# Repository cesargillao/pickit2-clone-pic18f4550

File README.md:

# Clon del Programador de PIC PicKit 2 con PIC18F4550

## Se proporciona:
* Diagrama esquemático para emular el funcionamiento (Proteus)
* Diagrama esquemático y PCB (CadSoft Eagle)
* Software en C y ASM con su respectivo HEX (CCS Compiler)

### Si te gusta el proyecto, recomiendo dejar una estrella en el mismo o en mi perfil.
### Eso me inspira a seguir colaborando a la comunidad ❤.

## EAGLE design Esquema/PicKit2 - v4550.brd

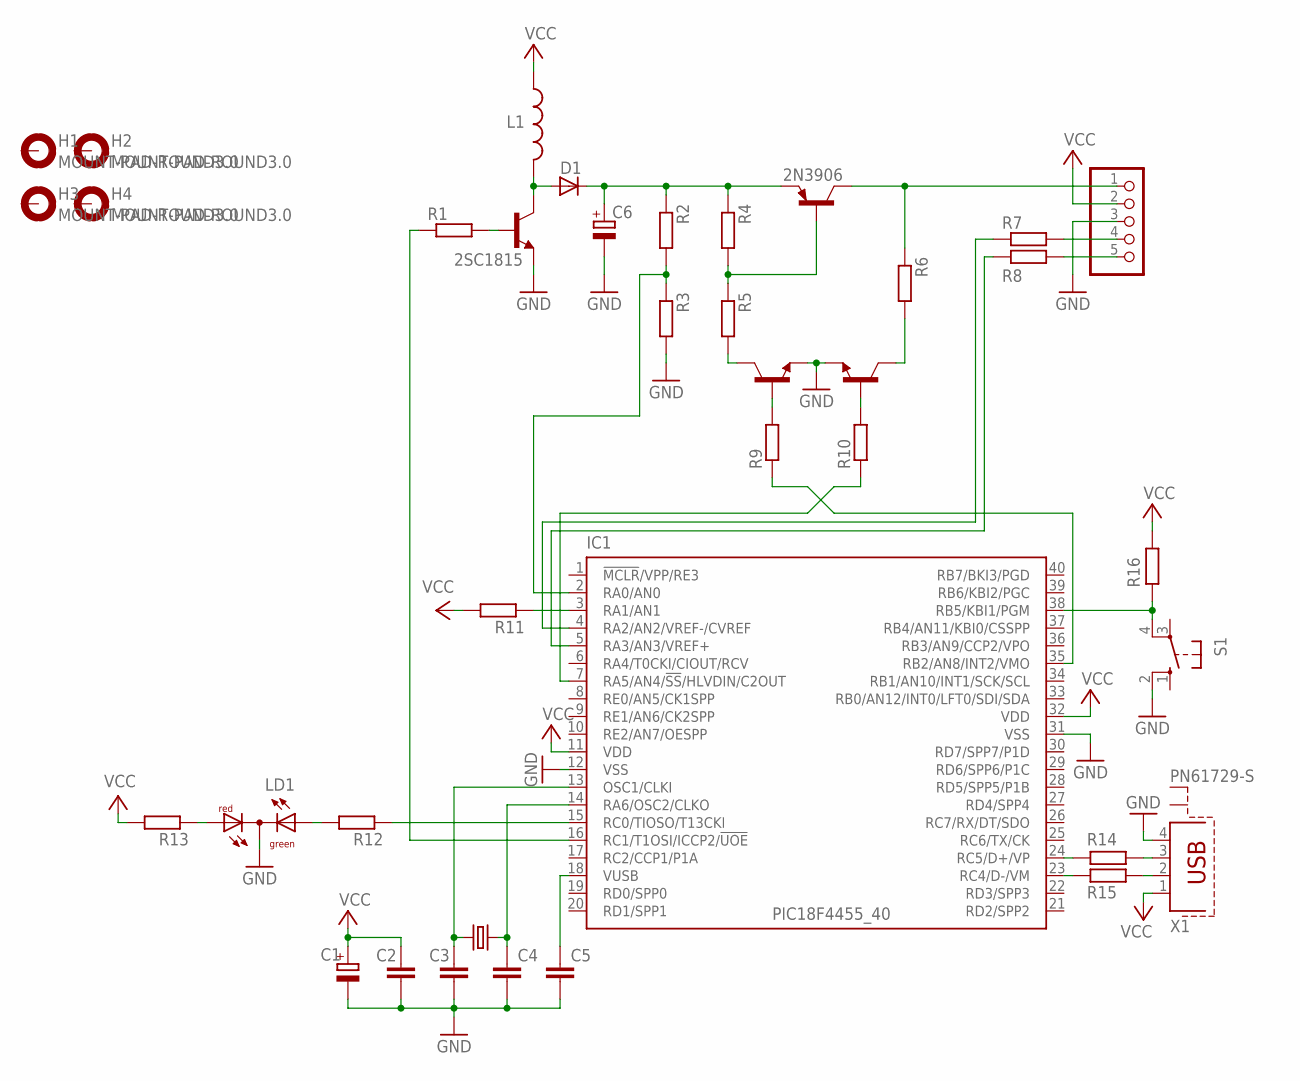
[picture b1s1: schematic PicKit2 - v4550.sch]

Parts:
C1, C6: CPOL-EUE2,5-6E; E2,5-6E
C2, C3, C4, C5: C-EU050-025X075; C050-025X075
D1: 1N4148DO35-10; DO35-10
H1, H2, H3, H4: MOUNT-PAD-ROUND3.0; 3,0-PAD
IC1: PIC18F4455_40; DIL40
JP1: PINHD-1X5/90; 1X05/90
L1: L-USIR-2; IR-2
LD1: DUOLED-RG-C; DUOLED-C-5MM
Q1: 2N3906; TO92
R1, R2, R3, R4, R5, R6, R7, R8, R9, R10, R11, R12, R13, R14, R15, R16: R-EU_0207/10; 0207/10
S1: 10-XX; B3F-10XX
T1, T2, T3: 2SC1815; TO92-ECB
X1: PN61729-S
Y1: CRYSTALHC49S; HC49/S

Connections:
GND: C1.-, C2.2, C3.2, C4.2, C5.2, C6.-, IC1.12 (VSS), IC1.31 (VSS), JP1.3, LD1.C, R3.2, S1.2 (S1), T1.E, T2.E, T3.E, X1.4
unnamed: R15.1, X1.2
unnamed: R14.1, X1.3
unnamed: IC1.23 (RC4/D-/VM), R15.2
unnamed: IC1.24 (RC5/D+/VP), R14.2
unnamed: D1.A, L1.2, T1.C
unnamed: IC1.2 (RA0/AN0), R2.2, R3.1
unnamed: C6.+, D1.C, Q1.3 (E), R2.1, R4.1
unnamed: Q1.2 (B), R4.2, R5.1
unnamed: R1.2, T1.B
unnamed: R6.2, T3.C
unnamed: JP1.1, Q1.1 (C), R6.1
unnamed: R9.2, T2.B
unnamed: R5.2, T2.C
unnamed: R10.2, T3.B
unnamed: IC1.7 (RA5/AN4/!SS!/HLVDIN/C2OUT), R10.1
unnamed: IC1.16 (RC1/T1OSI/ICCP2/!UOE), R1.1
unnamed: IC1.35 (RB2/AN8/INT2/VMO), R9.1
unnamed: JP1.5, R8.2
unnamed: JP1.4, R7.2
unnamed: IC1.4 (RA2/AN2/VREF-/CVREF), R7.1
unnamed: IC1.5 (RA3/AN3/VREF+), R8.1
unnamed: C3.1, IC1.13 (OSC1/CLKI), Y1.1
unnamed: C4.1, IC1.14 (RA6/OSC2/CLKO), Y1.2
unnamed: C5.1, IC1.18 (VUSB)
unnamed: IC1.38 (RB5/KBI1/PGM), R16.2, S1.4 (P1)
unnamed: IC1.3 (RA1/AN1), R11.1
unnamed: LD1.AR, R13.1
unnamed: LD1.AX (AG), R12.2
unnamed: IC1.15 (RC0/TIOSO/T13CKI), R12.1
VCC: C1.+, C2.1, IC1.11 (VDD), IC1.32 (VDD), JP1.2, L1.1, R11.2, R13.2, R16.1, X1.1

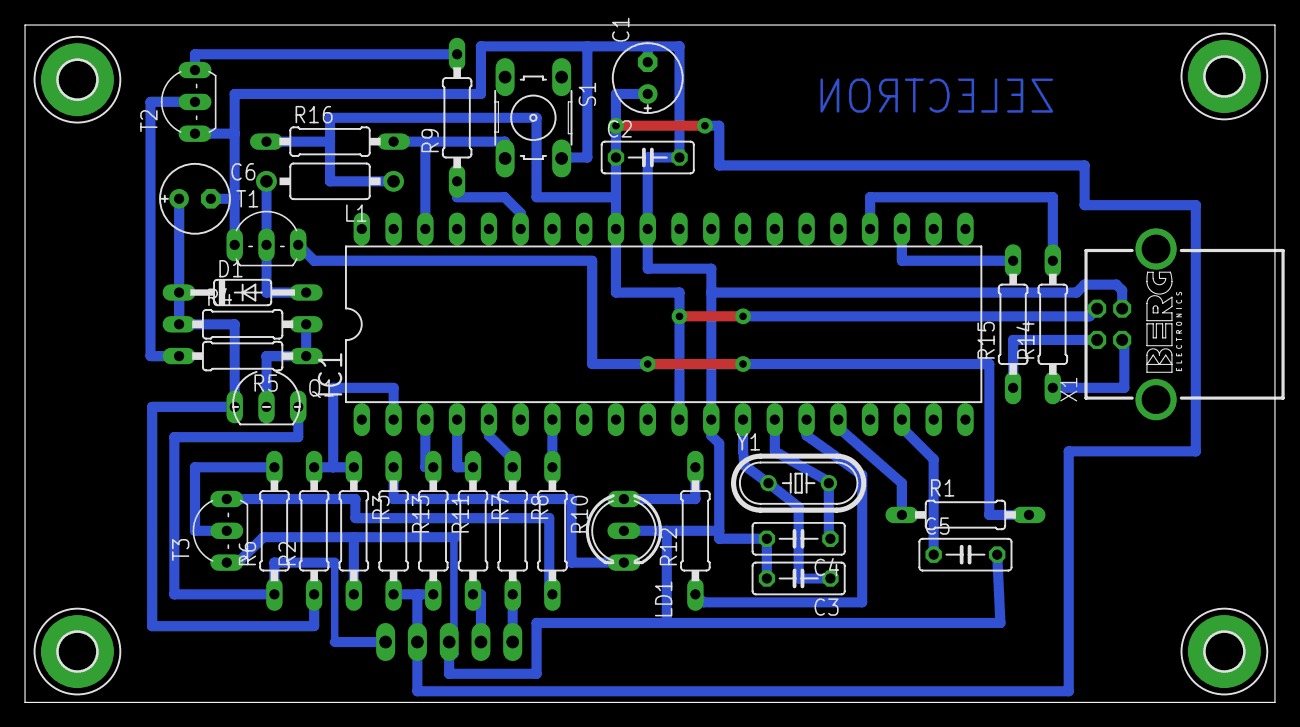
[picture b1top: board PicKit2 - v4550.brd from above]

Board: 2 copper layers, 99.9 x 54.2 mm, 38 parts (1 on the bottom side), 31 nets.

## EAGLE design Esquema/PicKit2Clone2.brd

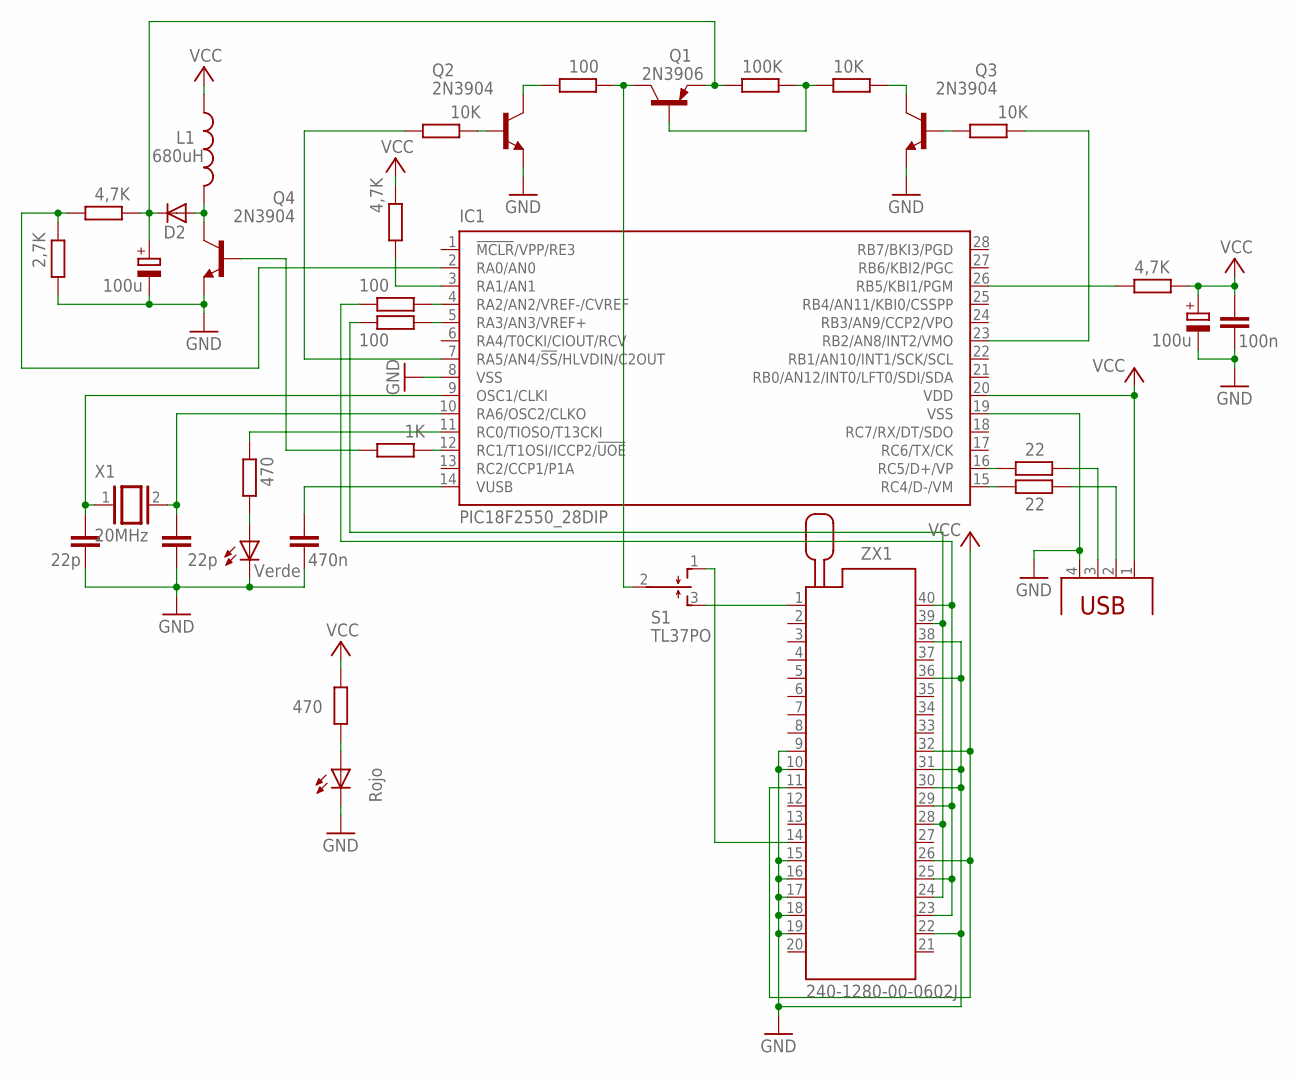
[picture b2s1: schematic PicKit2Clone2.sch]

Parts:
C1, C2: 22p; C075-032X103
C3: 100n; C075-032X103
C4, C6: 100u; E2,5-6E
C5: 470n; C075-032X103
D2: 1N4148DO35-7; DO35-7
IC1: PIC18F2550_28DIP; DIL28-3
L1: 680uH; 0207/7
LED1: Verde; LED3MM
LED2: Rojo; LED3MM
Q1: 2N3906; TO92
Q2, Q3, Q4: 2N3904; TO92
R1, R2: 22; 0207/7
R3, R4: 470; 0207/7
R5: 1K; 0207/7
R6: 2,7K; 0207/7
R7, R15, R16: 4,7K; 0207/7
R8: 100K; 0207/7
R9, R10, R14: 10K; 0207/7
R11, R12, R13: 100; 0207/7
S1: TL37PO; TL3XPO
USB: PN87520
X1: 20MHz; QS
ZX1: 240-1280-00-0602J

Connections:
GND: C1.2, C2.2, C3.1, C4.-, C5.1, C6.-, IC1.8 (VSS), IC1.19 (VSS), LED1.K (C), LED2.K (C), Q2.3 (E), Q3.3 (E), Q4.3 (E), R6.1, USB.4, ZX1.9, ZX1.10, ZX1.15, ZX1.16, ZX1.17, ZX1.18, ZX1.19, ZX1.22, ZX1.30, ZX1.31, ZX1.36, ZX1.38
unnamed: C2.1, IC1.10 (RA6/OSC2/CLKO), X1.2
unnamed: C1.1, IC1.9 (OSC1/CLKI), X1.1
unnamed: LED1.A, R3.1
unnamed: IC1.11 (RC0/TIOSO/T13CKI), R3.2
unnamed: C5.2, IC1.14 (VUSB)
unnamed: Q1.1 (C), R11.2, S1.2
unnamed: IC1.26 (RB5/KBI1/PGM), R7.1
unnamed: Q1.2 (B), R8.2, R10.1
unnamed: Q2.1 (C), R11.1
unnamed: R1.2, USB.2
unnamed: IC1.15 (RC4/D-/VM), R1.1
unnamed: IC1.16 (RC5/D+/VP), R2.1
unnamed: R2.2, USB.3
unnamed: IC1.3 (RA1/AN1), R15.1
unnamed: IC1.4 (RA2/AN2/VREF-/CVREF), R13.2
unnamed: Q3.1 (C), R10.2
unnamed: IC1.7 (RA5/AN4/!SS!/HLVDIN/C2OUT), R14.1
unnamed: Q2.2 (B), R14.2
unnamed: Q3.2 (B), R9.1
unnamed: IC1.23 (RB2/AN8/INT2/VMO), R9.2
unnamed: LED2.A, R4.1
unnamed: IC1.12 (RC1/T1OSI/ICCP2/!UOE), R5.2
unnamed: D2.A, L1.2, Q4.1 (C)
unnamed: C6.+, D2.C, Q1.3 (E), R8.1, R16.2
unnamed: IC1.2 (RA0/AN0), R6.2, R16.1
unnamed: Q4.2 (B), R5.1
unnamed: IC1.5 (RA3/AN3/VREF+), R12.2
unnamed: S1.1 (O), ZX1.14
unnamed: S1.3 (S), ZX1.1
unnamed: R12.1, ZX1.24, ZX1.28, ZX1.39
unnamed: R13.1, ZX1.23, ZX1.25, ZX1.29, ZX1.40
VCC: C3.2, C4.+, IC1.20 (VDD), L1.1, R4.2, R7.2, R15.2, USB.1, ZX1.11, ZX1.26, ZX1.32

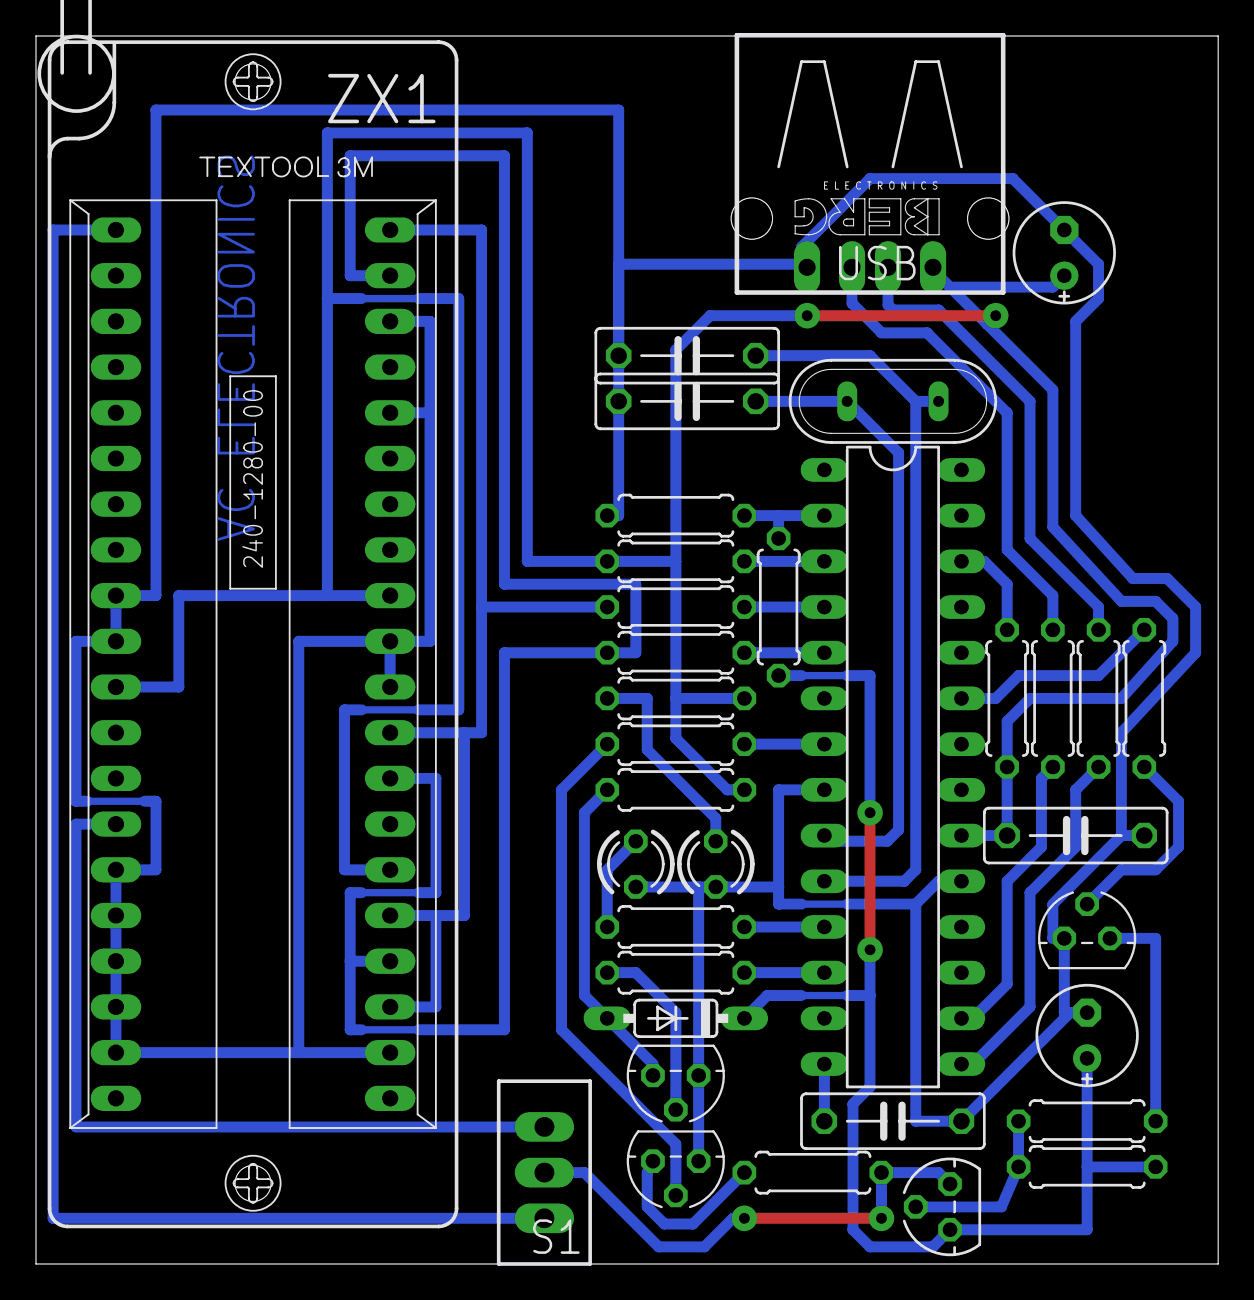
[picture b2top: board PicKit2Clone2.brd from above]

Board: 2 copper layers, 65.7 x 68.2 mm, 35 parts (0 on the bottom side), 33 nets.

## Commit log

2023-06-02 Agregado firmware compilado
